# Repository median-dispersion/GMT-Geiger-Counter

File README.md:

# GMT-Geiger-Counter

## ⚠️ DISCLAIMER

This is a hobby project and should not be relied upon to accurately determine radiation levels, especially not if those radiation levels are potentially dangerous and or lethal!

## 🖼️ Images

<p align="center">

    <br>

</p>

## 📸 Screenshots

<p align="center">

</p>

## ⚙️ Features, Settings & Usage

### Geiger counter

#### Main Screen

The main Geiger counter display shows the equivalent dose, a radiation intensity rating, the counts-per-minute reading, and the integration time. From this screen, you can also access and navigate to all other system functions.

| ID     | Description                                                                                                                                                                                                                                                                                                                                                        |
| ------ | ------------------------------------------------------------------------------------------------------------------------------------------------------------------------------------------------------------------------------------------------------------------------------------------------------------------------------------------------------------------ |
| **1**  | **Main Equivalent Dose Screen** - Displays the equivalent dose in your selected unit, calculated over the current integration time.                                                                                                                                                                                                                                |
| **2**  | Tap the equivalent dose display to open the Geiger counter information section.                                                                                                                                                                                                                                                                                    |
| **3**  | Shows the current **radiation rating**.                                                                                                                                                                                                                                                                                                                            |
| **4**  | Displays the **counts per minute (CPM)** reading for the current integration time.                                                                                                                                                                                                                                                                                 |
| **5**  | **Integration Time** - The number of seconds the Geiger counter averages measurements to calculate CPM and equivalent dose. Shorter integration times provide more precise readings at high radiation levels; longer times are better for low radiation levels. The counter automatically adjusts this setting but it can also be manually increased or decreased. |
| **6**  | Tap to open the **audio settings**.                                                                                                                                                                                                                                                                                                                                |
| **7**  | Tap to open the **display settings**.                                                                                                                                                                                                                                                                                                                              |
| **8**  | Tap to enter **sleep mode**, which turns off the display and mutes all buzzer sounds.                                                                                                                                                                                                                                                                              |
| **9**  | Tap to manually **decrease** the integration time.                                                                                                                                                                                                                                                                                                                 |
| **10** | Tap to **reset** the integration time to **automatic**.                                                                                                                                                                                                                                                                                                            |
| **11** | Tap to manually **increase** the integration time.                                                                                                                                                                                                                                                                                                                 |
| **12** | Tap to enable and open the **cosmic ray detector**.                                                                                                                                                                                                                                                                                                                |
| **13** | Tap to view **radiation history** in a graphical format.                                                                                                                                                                                                                                                                                                           |
| **14** | Tap to enable and open the **true random number generator**.                                                                                                                                                                                                                                                                                                       |
| **15** | Tap to open the **hotspot settings**.                                                                                                                                                                                                                                                                                                                              |
| **16** | Tap to open the **Wi-Fi settings**.                                                                                                                                                                                                                                                                                                                                |
| **17** | Tap to open the **system settings**.                                                                                                                                                                                                                                                                                                                               |

#### Geiger counter info screens

The Geiger counter info screen displays additional information about the recorded Geiger counter data, like the absolute number of counts or the total absorbed dose since power-on. In the settings section of this menu, you can also change Geiger counter properties like the measurement unit or if the measured value should auto-range.

| ID    | Descriptions                                                                                                                                                                                              |
| ----- | --------------------------------------------------------------------------------------------------------------------------------------------------------------------------------------------------------- |
| **1** | **Total number of counts / total absorbed dose** - A sum of all counts or the total absorbed dose recorded since the device was powered on. This value only increases when the Geiger counter is enabled. |
| **2** | **Main Tube Detections** - The total number of detections or the total absorbed dose by the main tube since power-on.                                                                                     |
| **3** | **Follower Tube Detections** - The total number of detections or the total absorbed dose by the follower tube since power-on.                                                                             |
| **4** | Tap to **view the previous page.**                                                                                                                                                                        |
| **5** | Tap to **view the next page.**                                                                                                                                                                            |
| **6** | Tap to **exit the Geiger counter info** and return to the Geiger counter screen.                                                                                                                          |

### Cosmic ray detector

The cosmic ray detector measures cosmic ray exposure by recording coincidence events, which are shown on this screen. While the detector is enabled, its data is also available via the serial console, the wireless API interface and the log file.

| ID    | Description                                                                                                                                                                                                                          |
| ----- | ------------------------------------------------------------------------------------------------------------------------------------------------------------------------------------------------------------------------------------ |
| **1** | **Main Coincidence Events Screen** - Shows the total number of coincidence events recorded since the cosmic ray detector was enabled. This value resets when the cosmic ray detector is disabled.                                    |
| **2** | **Coincidence Events per Hour** - Displays the hourly average since the cosmic ray detector was enabled. This value resets when the cosmic ray detector is disabled.                                                                 |
| **3** | **Total Coincidence Events (Since Power-On)** - A sum of all coincidence events recorded since the device was powered on. This value only increases when the cosmic ray detector is enabled, but does not reset when it is disabled. |
| **4** | Tap to **temporarily mute detection sounds**. Tap again to re-enable them. This only mutes regular detection sounds; other alerts will still play.                                                                                   |
| **5** | Tap to enter **sleep mode**, which turns off the display and mutes all buzzer sounds.                                                                                                                                                |
| **6** | **Main Tube Detections** - The total number of detections by the main tube since the cosmic ray detector was enabled. This value resets when the cosmic ray detector is disabled.                                                    |
| **7** | **Follower Tube Detections** - The total number of detections by the follower tube since the cosmic ray detector was enabled. This value resets when the cosmic ray detector is disabled.                                            |
| **8** | Tap to **exit the cosmic ray detector** and return to the Geiger counter screen. A prompt will ask whether to disable the detector or keep it running in the background.                                                             |

### True random number generator

The true random number generator produces truly random numbers. You can set a custom range from 1 to 99, then roll to generate a number, which appears on the main result screen. While the generator is enabled, the Geiger counter is disabled. During this time, a continuous stream of random bits is also available via the serial console and wireless API interface.

| ID     | Description                                                                                                                                        |
| ------ | -------------------------------------------------------------------------------------------------------------------------------------------------- |
| **1**  | **Main Result Screen** - Displays a true random number once the roll is complete.                                                                  |
| **2**  | Tap to **increase the minimum value** of the result range.                                                                                         |
| **3**  | Tap to **increase the maximum value** of the result range.                                                                                         |
| **4**  | Shows the **minimum value** in the result range.                                                                                                   |
| **5**  | Shows the **maximum value** in the result range.                                                                                                   |
| **6**  | Tap to **decrease the minimum value** of the result range.                                                                                         |
| **7**  | Tap to **decrease the maximum value** of the result range.                                                                                         |
| **8**  | Tap to **roll a random number**.                                                                                                                   |
| **9**  | Tap to **temporarily mute detection sounds**. Tap again to re-enable them. This only mutes regular detection sounds; other alerts will still play. |
| **10** | Tap to enter **sleep mode**, which turns off the display and mutes all buzzer sounds.                                                              |
| **11** | Tap to **disable the true random number generator** and return to the Geiger counter screen.                                                       |

## ☁️ Web-App

All data recorded by the Geiger counter can also be accessed through a dedicated web app, which works in any modern browser on both PCs and smartphones. The app’s interface closely mirrors the main display on the Geiger counter itself, while also providing additional features such as extended graphical history with smoothing options. It is also required for tasks like updating Wi-Fi credentials.

To use the web app, an SD card containing the necessary files from the [firmware](Firmware/GMT-Geiger-Counter/SD%20Card/) folder must be inserted. Even without the app, the wireless API remains available, allowing data to be accessed through a browser; however, without the web app, the information will not be presented in a user-friendly format.

Screenshots of the web app can be found in the [screenshots](#-Screenshots) section.

## 🧩 Tube Compatibility

The tube driver PCB is compatible with a variety of Geiger-Müller tubes. Any tube that has a total length including the contacts of **110mm** to **107mm** or **90mm** to **87mm** and operates around **400V DC** should be physically compatible. Here are some tubes that will be compatible with this Geiger counter:

| Tube       | Compatible | Tested | Note                                          |
| ---------- | ---------- | ------ | --------------------------------------------- |
| SBM-20     | ✅          | ✅      | The tube this Geiger counter was designed for |
| STS-5      | ✅          | ❌      | The predecessor tube to the SBM-20            |
| J305 107mm | ✅          | ❌      | A modern alternative to the SBM-20            |
| J305 90mm  | ✅          | ❌      | A shorter version of the J305 107mm           |
| M4011      | ✅          | ❌      | An alternative to the J305 90mm               |

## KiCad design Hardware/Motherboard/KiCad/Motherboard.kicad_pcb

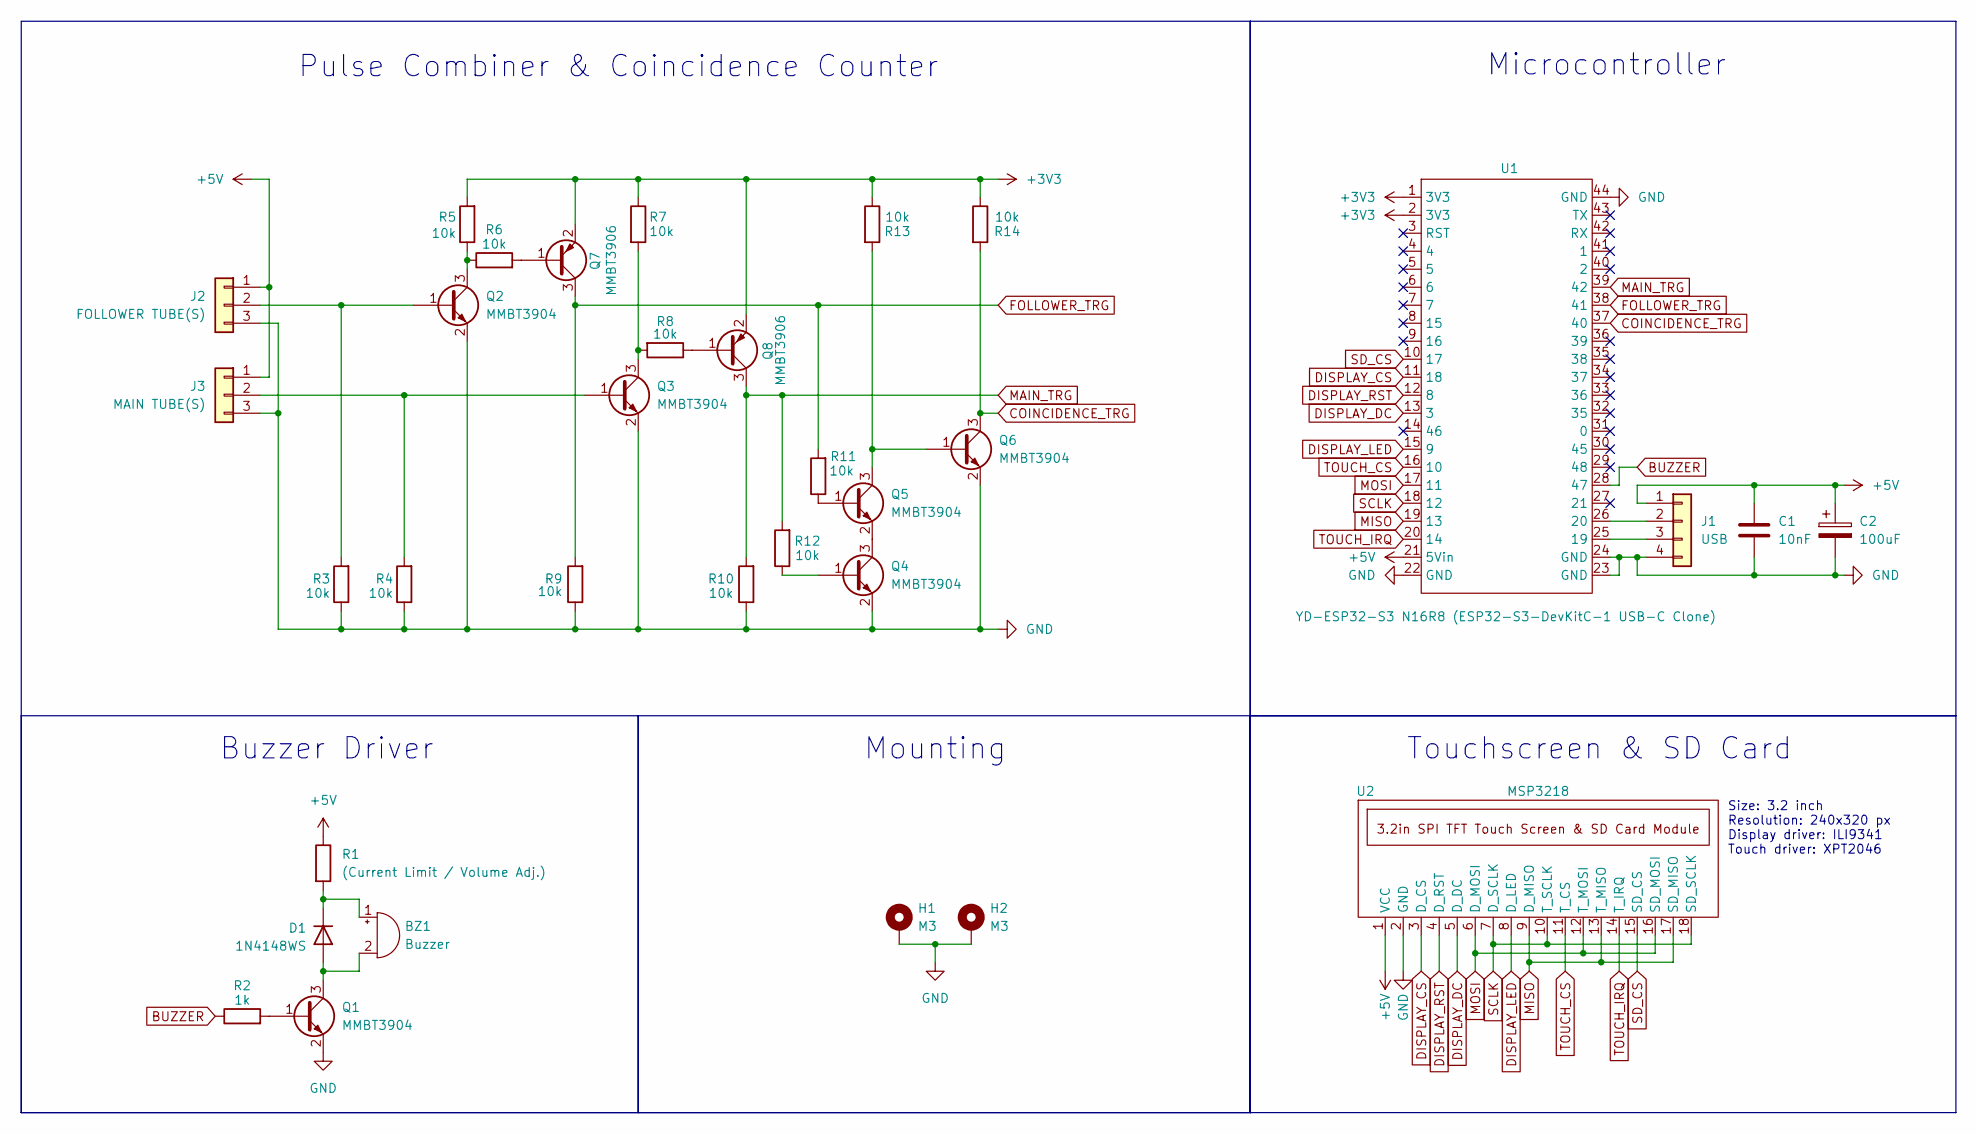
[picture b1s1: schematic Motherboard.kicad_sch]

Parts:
BZ1: Buzzer; PinHeader_1x02_P2.54mm_Vertical; MPN WT-1209T
C1: 10nF; C_1206_3216Metric_Pad1.33x1.80mm_HandSolder; MPN 885012208112
C2: 100uF; CP_Elec_6.3x5.4; MPN 875105344010
D1: 1N4148WS; D_SOD-323_HandSoldering; MPN 1N4148WS
H1, H2: M3; MountingHole_3.2mm_M3_Pad_Via
J1: USB; USB_Pin_Header; MPN PH1RB-04-UA
J2: FOLLOWER TUBE(S); PinHeader_1x03_P2.54mm_Vertical; MPN PH1RB-03-UA
J3: MAIN TUBE(S); PinHeader_1x03_P2.54mm_Vertical; MPN PH1RB-03-UA
Q1, Q2, Q3, Q4, Q5, Q6: MMBT3904; SOT-23_Handsoldering; MPN MMBT3904
Q7, Q8: MMBT3906; SOT-23_Handsoldering; MPN MMBT3906
R1: (Current Limit / Volume Adj.); R_1206_3216Metric_Pad1.30x1.75mm_HandSolder; MPN RC1206JR-070RL
R2: 1k; R_1206_3216Metric_Pad1.30x1.75mm_HandSolder; MPN RC1206FR-071KL
R3, R4, R5, R6, R7, R8, R9, R10, R11, R12, R13, R14: 10k; R_1206_3216Metric_Pad1.30x1.75mm_HandSolder; MPN RC1206FR-1310KL
U1: YD-ESP32-S3 N16R8 (ESP32-S3-DevKitC-1 USB-C Clone); YD-ESP32-S3_(ESP32-S3-DevKitC-1_USB-C_Clone); MPN YD-ESP32-S3 N16R8
U2: MSP3218; 3.2in_SPI_TFT_Touch_Screen_&_SD_Card_Module; MPN MSP3218

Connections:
+3V3: Q7.2 (E), Q8.2 (E), R5.2, R7.1, R13.1, R14.1, U1.1 (3V3), U1.2 (3V3)
+5V: C1.1, C2.1, J1.1, J2.1, J3.1, R1.1, U1.21 (5Vin), U2.1 (VCC)
BUZZER: R2.1, U1.28 (47)
COINCIDENCE_TRG: Q6.3 (C), R14.2, U1.37 (40)
DISPLAY_CS: U1.11 (18), U2.3 (D_CS)
DISPLAY_DC: U1.13 (3), U2.5 (D_DC)
DISPLAY_LED: U1.15 (9), U2.8 (D_LED)
DISPLAY_RST: U1.12 (8), U2.4 (D_RST)
FOLLOWER_TRG: Q7.3 (C), R9.2, R11.2, U1.38 (41)
GND: C1.2, C2.2, H1.1, H2.1, J1.4, J2.3, J3.3, Q1.2 (E), Q2.2 (E), Q3.2 (E), Q4.2 (E), Q6.2 (E), R3.1, R4.1, R9.1, R10.1, U1.22 (GND), U1.23 (GND), U1.24 (GND), U1.44 (GND), U2.2 (GND)
MAIN_TRG: Q8.3 (C), R10.2, R12.2, U1.39 (42)
MISO: U1.19 (13), U2.9 (D_MISO), U2.13 (T_MISO), U2.17 (SD_MISO)
MOSI: U1.17 (11), U2.6 (D_MOSI), U2.12 (T_MOSI), U2.16 (SD_MOSI)
unnamed: BZ1.1 (+), D1.1 (K), R1.2
unnamed: BZ1.2 (-), D1.2 (A), Q1.3 (C)
unnamed: J1.2, U1.26 (20)
unnamed: J1.3, U1.25 (19)
unnamed: J2.2, Q2.1 (B), R3.2
unnamed: J3.2, Q3.1 (B), R4.2
unnamed: Q1.1 (B), R2.2
unnamed: Q2.3 (C), R5.1, R6.1
unnamed: Q3.3 (C), R7.2, R8.2
unnamed: Q4.1 (B), R12.1
unnamed: Q4.3 (C), Q5.2 (E)
unnamed: Q5.1 (B), R11.1
unnamed: Q5.3 (C), Q6.1 (B), R13.2
unnamed: Q7.1 (B), R6.2
unnamed: Q8.1 (B), R8.1
SCLK: U1.18 (12), U2.7 (D_SCLK), U2.10 (T_SCLK), U2.18 (SD_SCLK)
SD_CS: U1.10 (17), U2.15 (SD_CS)
TOUCH_CS: U1.16 (10), U2.11 (T_CS)
TOUCH_IRQ: U1.20 (14), U2.14 (T_IRQ)

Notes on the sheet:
Microcontroller
Mounting
Buzzer Driver
Touchscreen & SD Card
Size: 3.2 inch Resolution: 240x320 px Display driver: ILI9341 Touch driver: XPT2046
Pulse Combiner & Coincidence Counter

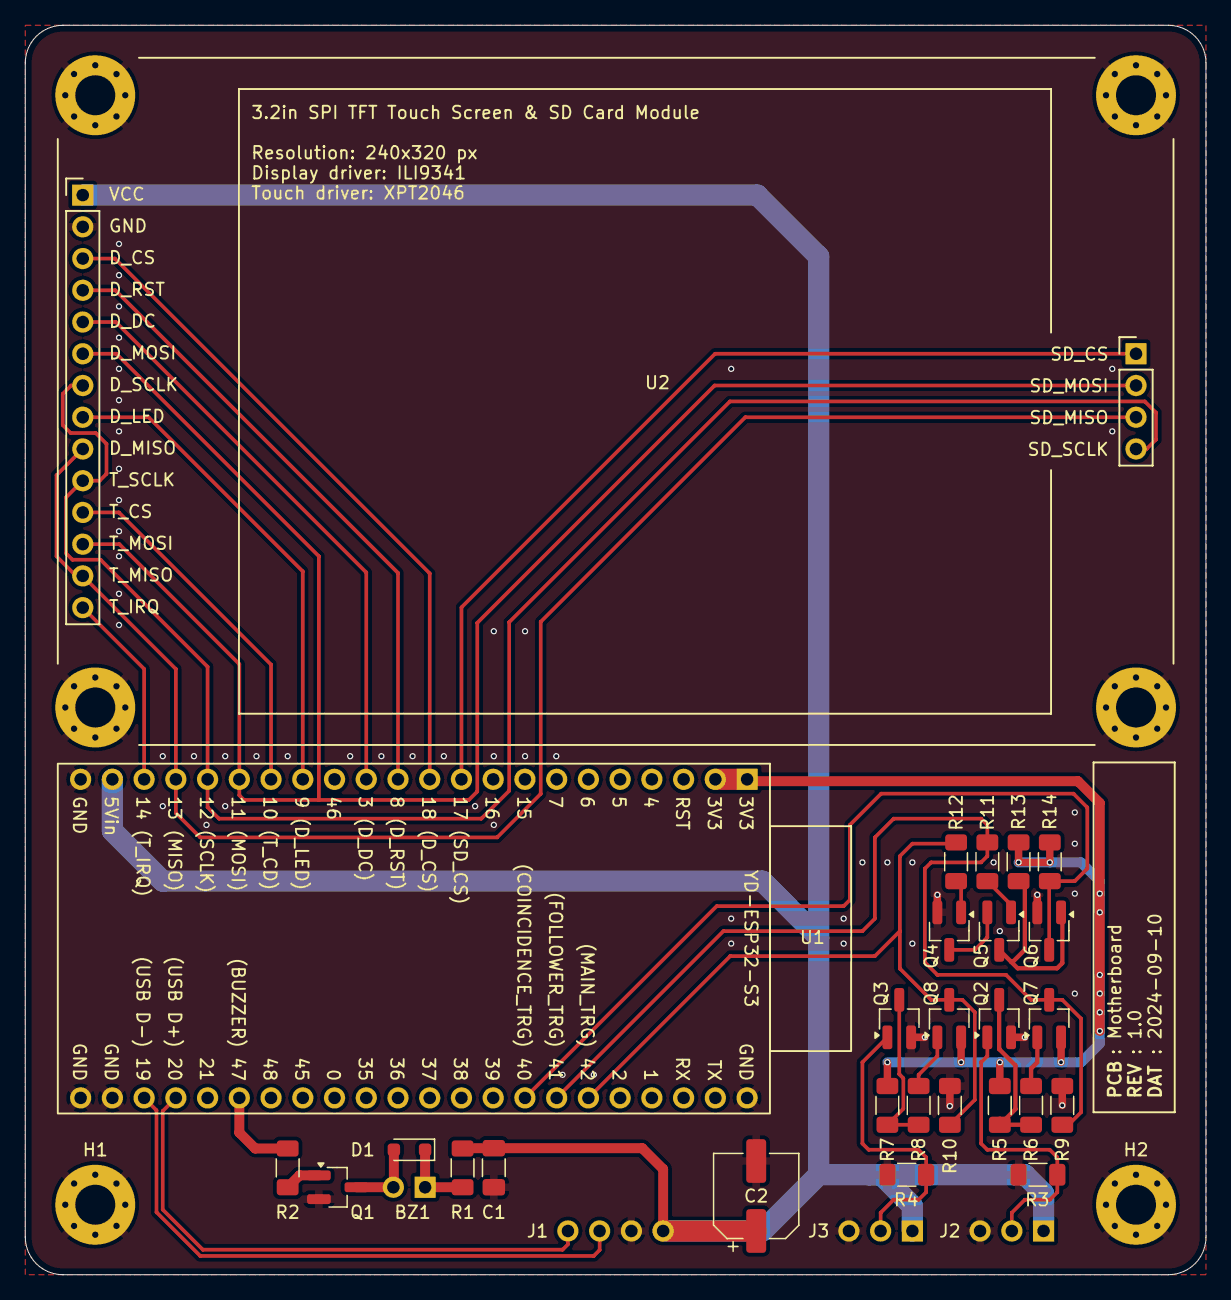
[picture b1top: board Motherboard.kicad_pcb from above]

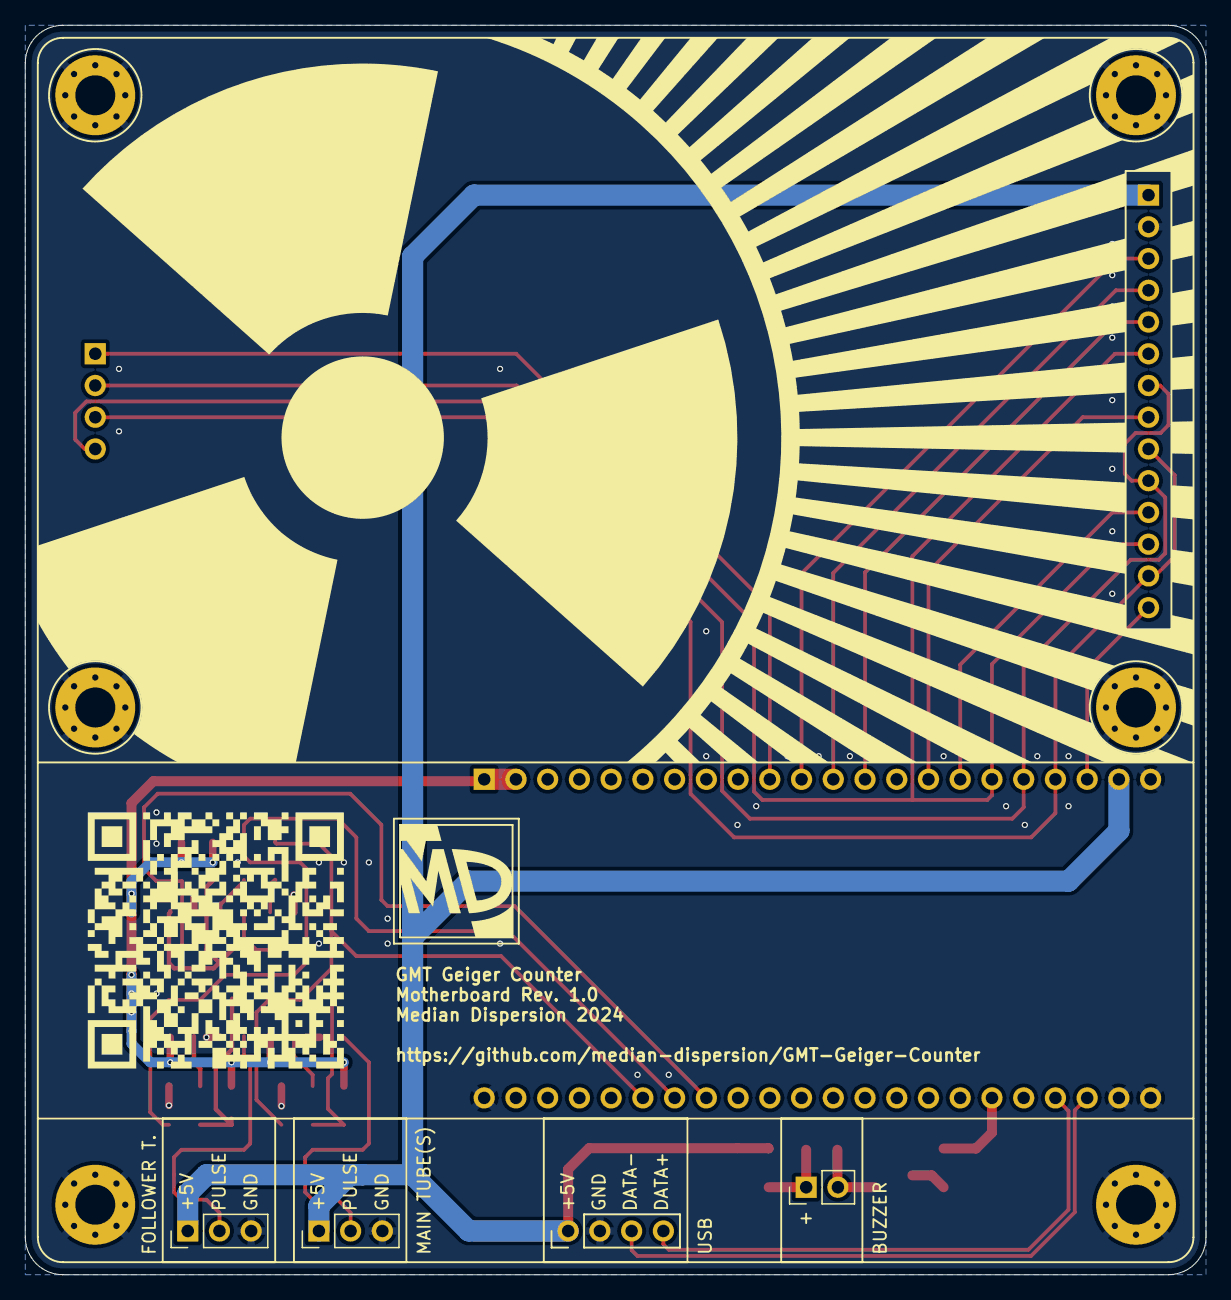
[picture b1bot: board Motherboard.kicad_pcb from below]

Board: 2 copper layers, 94.5 x 100.0 mm, 33 parts (4 on the bottom side), 32 nets.

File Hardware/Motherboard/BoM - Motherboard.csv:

"Reference","Value","Qty","Footprint","MPN","Datasheet","DigiKey","Price (EUR)"
"BZ1","Buzzer","1","Connector_PinHeader_2.54mm:PinHeader_1x02_P2.54mm_Vertical","WT-1209T","https://www.soberton.com/wp-content/uploads/2022/03/WT-1209T.pdf","https://www.digikey.com/en/products/detail/soberton-inc/WT-1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","0,39€"
"C1","10nF","1","Capacitor_SMD:C_1206_3216Metric_Pad1.33x1.80mm_HandSolder","885012208112","https://www.we-online.com/components/products/datasheet/8850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","https://www.digikey.com/en/products/detail/w%C3%BCrth-elektr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 ","0,1€ "
"C2","100uF","1","Capacitor_SMD:CP_Elec_6.3x5.4","875105344010","https://www.we-online.com/components/products/datasheet/8751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","https://www.digikey.com/en/products/detail/würth-elektronik/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 ","0,62€"
"D1","1N4148WS","1","Diode_SMD:D_SOD-323_HandSoldering","1N4148WS","https://www.smc-diodes.com/propdf/1N4148WS%20N0572%20REV.B.pdf","https://www.digikey.com/en/products/detail/smc-diode-solutio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","0,09€"
"J1","USB","1","Footprints:USB_Pin_Header","PH1RB-04-UA","https://app.adam-tech.com/products/download/data_sheet/20128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","https://www.digikey.com/en/products/detail/adam-tech/PH1RB-0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","0,14€"
"J2","FOLLOWER TUBE(S)","1","Connector_PinHeader_2.54mm:PinHeader_1x03_P2.54mm_Vertical","PH1RB-03-UA","https://app.adam-tech.com/products/download/data_sheet/20128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","https://www.digikey.com/en/products/detail/adam-tech/PH1RB-0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","0,11€"
"J3","MAIN TUBE(S)","1","Connector_PinHeader_2.54mm:PinHeader_1x03_P2.54mm_Vertical","PH1RB-03-UA","https://app.adam-tech.com/products/download/data_sheet/20128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","https://www.digikey.com/en/products/detail/adam-tech/PH1RB-0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","0,11€"
"Q1","MMBT3904","1","Package_TO_SOT_SMD:SOT-23_Handsoldering","MMBT3904","https://goodarksemi.com/docs/datasheets/transistors/MMBT3904.pdf","https://www.digikey.com/en/products/detail/good-ark-semicond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","0,09€"
"Q2","MMBT3904","1","Package_TO_SOT_SMD:SOT-23_Handsoldering","MMBT3904","https://goodarksemi.com/docs/datasheets/transistors/MMBT3904.pdf","https://www.digikey.com/en/products/detail/good-ark-semicond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","0,09€"
"Q3","MMBT3904","1","Package_TO_SOT_SMD:SOT-23_Handsoldering","MMBT3904","https://goodarksemi.com/docs/datasheets/transistors/MMBT3904.pdf","https://www.digikey.com/en/products/detail/good-ark-semicond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","0,09€"
"Q4","MMBT3904","1","Package_TO_SOT_SMD:SOT-23_Handsoldering","MMBT3904","https://goodarksemi.com/docs/datasheets/transistors/MMBT3904.pdf","https://www.digikey.com/en/products/detail/good-ark-semicond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","0,09€"
"Q5","MMBT3904","1","Package_TO_SOT_SMD:SOT-23_Handsoldering","MMBT3904","https://goodarksemi.com/docs/datasheets/transistors/MMBT3904.pdf","https://www.digikey.com/en/products/detail/good-ark-semicond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","0,09€"
"Q6","MMBT3904","1","Package_TO_SOT_SMD:SOT-23_Handsoldering","MMBT3904","https://goodarksemi.com/docs/datasheets/transistors/MMBT3904.pdf","https://www.digikey.com/en/products/detail/good-ark-semicond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","0,09€"
"Q7","MMBT3906","1","Package_TO_SOT_SMD:SOT-23_Handsoldering","MMBT3906","https://goodarksemi.com/docs/datasheets/transistors/MMBT3906.pdf","https://www.digikey.com/en/products/detail/good-ark-semicond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","0,09€"
"Q8","MMBT3906","1","Package_TO_SOT_SMD:SOT-23_Handsoldering","MMBT3906","https://goodarksemi.com/docs/datasheets/transistors/MMBT3906.pdf","https://www.digikey.com/en/products/detail/good-ark-semicond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","0,09€"
"R1","(Current Limit / Volume Adj.)","1","Resistor_SMD:R_1206_3216Metric_Pad1.30x1.75mm_HandSolder","RC1206JR-070RL","https://www.yageo.com/upload/media/product/products/datashee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","https://www.digikey.com/en/products/detail/yageo/RC1206JR-07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","0,09€"
"R2","1k","1","Resistor_SMD:R_1206_3216Metric_Pad1.30x1.75mm_HandSolder","RC1206FR-071KL","https://www.yageo.com/upload/media/product/products/datashee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","https://www.digikey.com/en/products/detail/yageo/RC1206FR-07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","0,09€"
"R3","10k","1","Resistor_SMD:R_1206_3216Metric_Pad1.30x1.75mm_HandSolder","RC1206FR-1310KL","https://www.yageo.com/upload/media/product/products/datashee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","https://www.digikey.com/en/products/detail/yageo/RC1206FR-13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","0,09€"
"R4","10k","1","Resistor_SMD:R_1206_3216Metric_Pad1.30x1.75mm_HandSolder","RC1206FR-1310KL","https://www.yageo.com/upload/media/product/products/datashee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","https://www.digikey.com/en/products/detail/yageo/RC1206FR-13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","0,09€"
"R5","10k","1","Resistor_SMD:R_1206_3216Metric_Pad1.30x1.75mm_HandSolder","RC1206FR-1310KL","https://www.yageo.com/upload/media/product/products/datashee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","https://www.digikey.com/en/products/detail/yageo/RC1206FR-13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","0,09€"
"R6","10k","1","Resistor_SMD:R_1206_3216Metric_Pad1.30x1.75mm_HandSolder","RC1206FR-1310KL","https://www.yageo.com/upload/media/product/products/datashee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","https://www.digikey.com/en/products/detail/yageo/RC1206FR-13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","0,09€"
"R7","10k","1","Resistor_SMD:R_1206_3216Metric_Pad1.30x1.75mm_HandSolder","RC1206FR-1310KL","https://www.yageo.com/upload/media/product/products/datashee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","https://www.digikey.com/en/products/detail/yageo/RC1206FR-13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","0,09€"
"R8","10k","1","Resistor_SMD:R_1206_3216Metric_Pad1.30x1.75mm_HandSolder","RC1206FR-1310KL","https://www.yageo.com/upload/media/product/products/datashee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","https://www.digikey.com/en/products/detail/yageo/RC1206FR-13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","0,09€"
"R9","10k","1","Resistor_SMD:R_1206_3216Metric_Pad1.30x1.75mm_HandSolder","RC1206FR-1310KL","https://www.yageo.com/upload/media/product/products/datashee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","https://www.digikey.com/en/products/detail/yageo/RC1206FR-13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","0,09€"
"R10","10k","1","Resistor_SMD:R_1206_3216Metric_Pad1.30x1.75mm_HandSolder","RC1206FR-1310KL","https://www.yageo.com/upload/media/product/products/datashee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","https://www.digikey.com/en/products/detail/yageo/RC1206FR-13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","0,09€"
"R11","10k","1","Resistor_SMD:R_1206_3216Metric_Pad1.30x1.75mm_HandSolder","RC1206FR-1310KL","https://www.yageo.com/upload/media/product/products/datashee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","https://www.digikey.com/en/products/detail/yageo/RC1206FR-13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","0,09€"
"R12","10k","1","Resistor_SMD:R_1206_3216Metric_Pad1.30x1.75mm_HandSolder","RC1206FR-1310KL","https://www.yageo.com/upload/media/product/products/datashee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","https://www.digikey.com/en/products/detail/yageo/RC1206FR-13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","0,09€"
"R13","10k","1","Resistor_SMD:R_1206_3216Metric_Pad1.30x1.75mm_HandSolder","RC1206FR-1310KL","https://www.yageo.com/upload/media/product/products/datashee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","https://www.digikey.com/en/products/detail/yageo/RC1206FR-13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","0,09€"
"R14","10k","1","Resistor_SMD:R_1206_3216Metric_Pad1.30x1.75mm_HandSolder","RC1206FR-1310KL","https://www.yageo.com/upload/media/product/products/datashee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","https://www.digikey.com/en/products/detail/yageo/RC1206FR-13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","0,09€"
"U1","YD-ESP32-S3 N16R8 (ESP32-S3-DevKitC-1 USB-C Clone)","1","Footprints:YD-ESP32-S3_(ESP32-S3-DevKitC-1_USB-C_Clone)","YD-ESP32-S3 N16R8","https://github.com/vcc-gnd/YD-ESP32-S3","~","8€"
"U2","MSP3218","1","Footprints:3.2in_SPI_TFT_Touch_Screen_&_SD_Card_Module","MSP3218","~","~","12€"

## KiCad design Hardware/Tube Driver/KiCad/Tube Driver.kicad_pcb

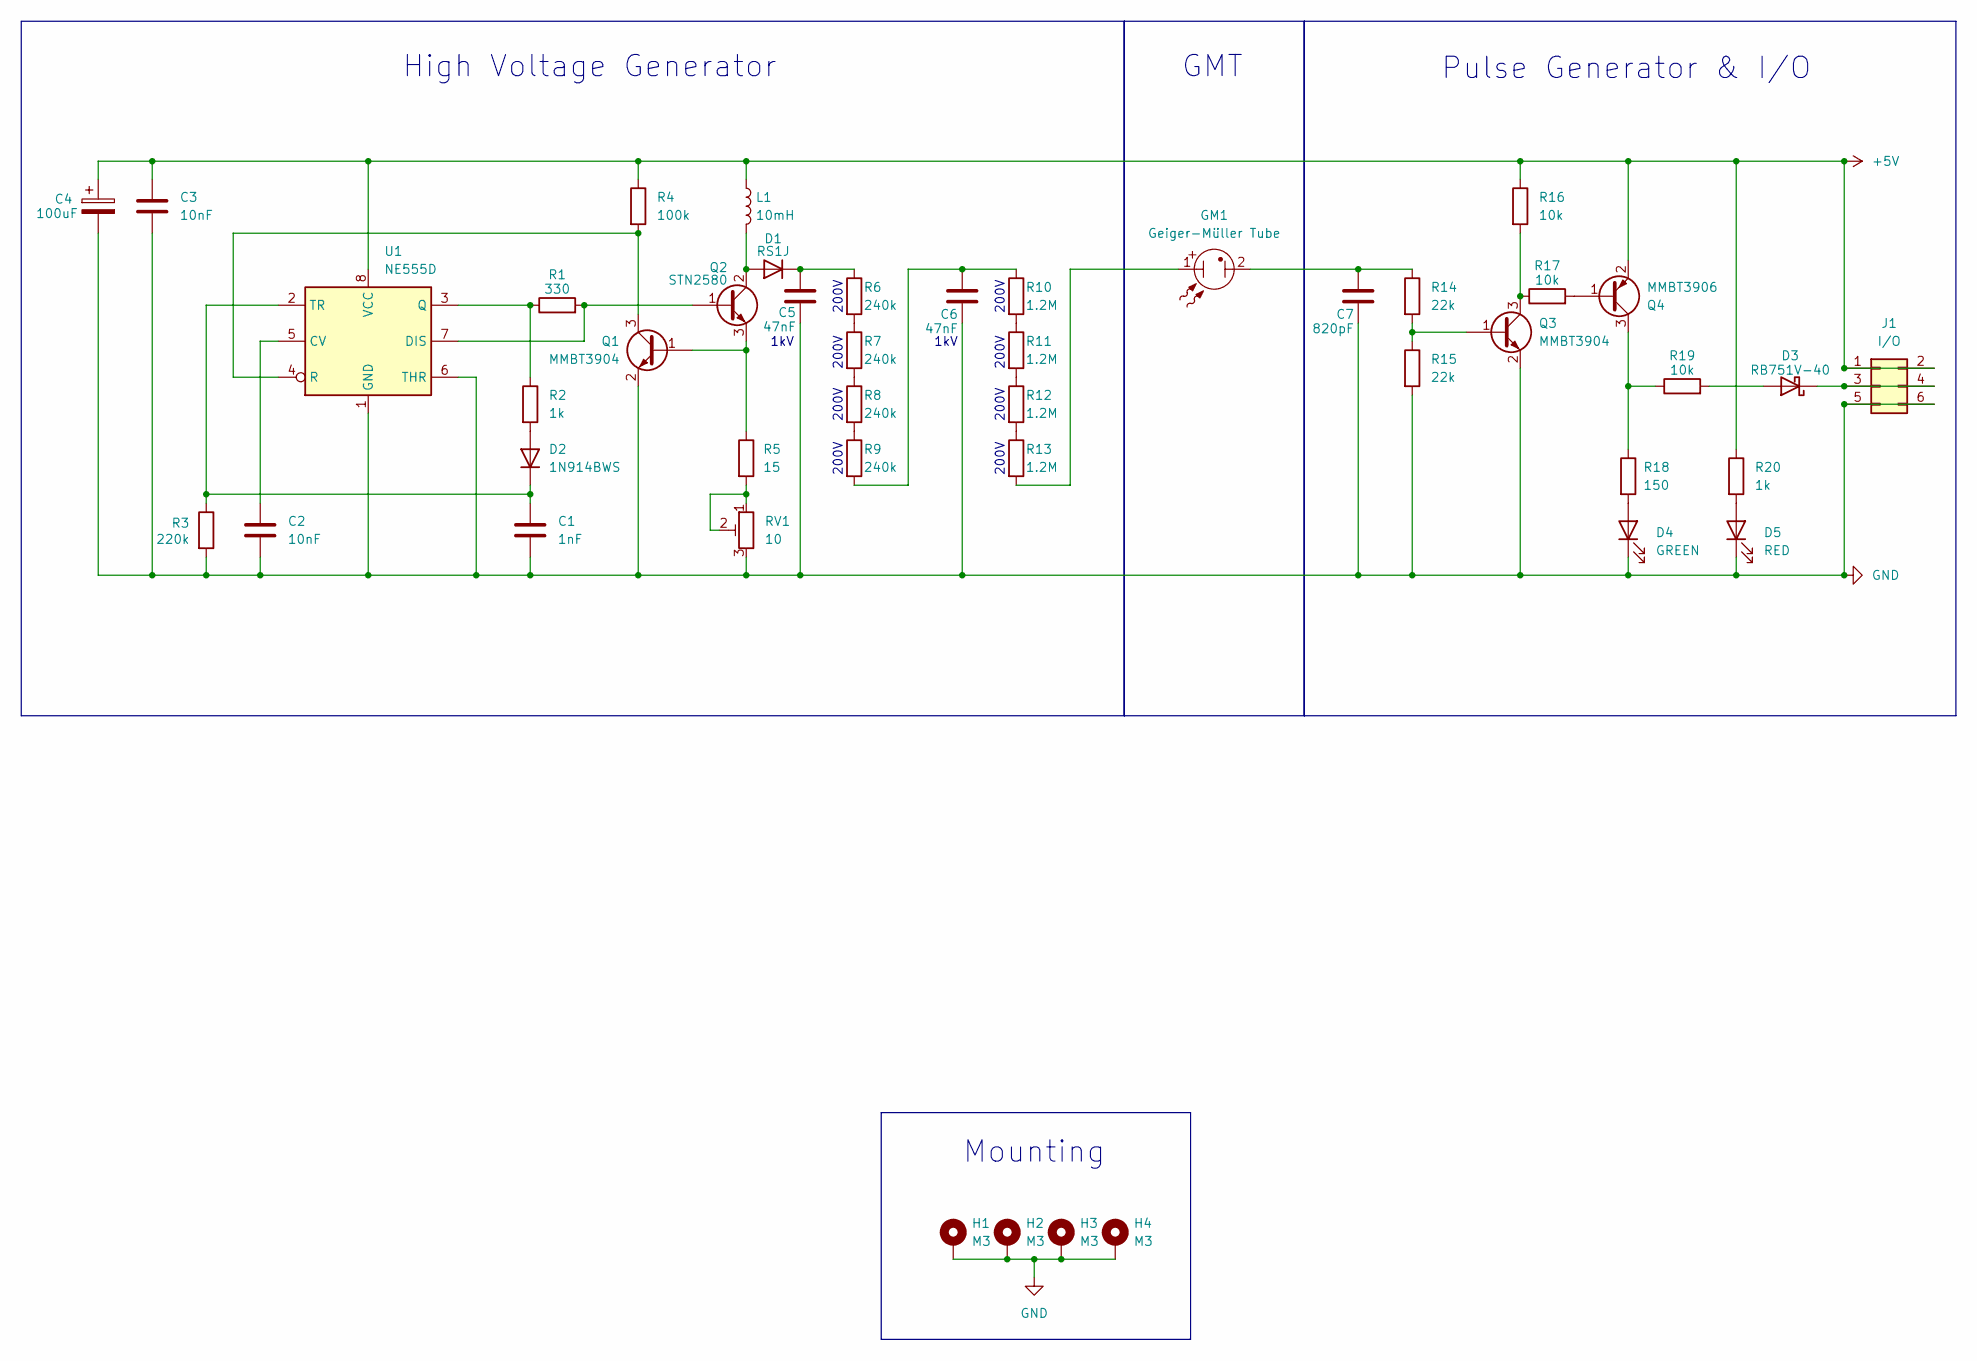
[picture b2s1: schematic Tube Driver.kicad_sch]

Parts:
C1: 1nF; C_1206_3216Metric_Pad1.33x1.80mm_HandSolder; MPN 885012208046
C2, C3: 10nF; C_1206_3216Metric_Pad1.33x1.80mm_HandSolder; MPN 885012208112
C4: 100uF; CP_Elec_6.3x5.4; MPN 865080243007
C5, C6: 47nF; C_1210_3225Metric_Pad1.33x2.70mm_HandSolder; MPN C1210V473KDRAC7800
C7: 820pF; C_1206_3216Metric_Pad1.33x1.80mm_HandSolder; MPN CC1206FRNPO9BN821
D1: RS1J; D_SMA_HV_Handsoldering; MPN RS1J-13-F
D2: 1N914BWS; D_SOD-323_HandSoldering; MPN 1N914BWS
D3: RB751V-40; D_SOD-323_HandSoldering; MPN RB751V-40_R1_00001
D4: GREEN; LED_1206_3216Metric_Pad1.42x1.75mm_HandSolder; MPN 150120GS75000
D5: RED; LED_1206_3216Metric_Pad1.42x1.75mm_HandSolder; MPN 150120RS75000
GM1: Geiger-Müller Tube; GM_Tube_Mount; MPN FC-102 BRIGHT TIN
H1, H2, H3, H4: M3; MountingHole_3.2mm_M3_Pad_Via
J1: I/O; PinHeader_2x03_P2.54mm_Vertical; MPN PH2-06-UA
L1: 10mH; L_8065_HandSolder; MPN 74404086103
Q1, Q3: MMBT3904; SOT-23_Handsoldering; MPN MMBT3904
Q2: STN2580; SOT-223; MPN STN2580
Q4: MMBT3906; SOT-23_Handsoldering; MPN MMBT3906
R1: 330; R_1206_3216Metric_Pad1.30x1.75mm_HandSolder; MPN RC1206FR-07330RL
R2, R20: 1k; R_1206_3216Metric_Pad1.30x1.75mm_HandSolder; MPN RC1206FR-071KL
R3: 220k; R_1206_3216Metric_Pad1.30x1.75mm_HandSolder; MPN RC1206FR-07220KL
R4: 100k; R_1206_3216Metric_Pad1.30x1.75mm_HandSolder; MPN AC1206FR-07100KL
R5: 15; R_1206_3216Metric_Pad1.30x1.75mm_HandSolder; MPN RC1206FR-0715RL
R6, R7, R8, R9: 240k; R_1206_3216Metric_Pad1.30x1.75mm_HandSolder; MPN RC1206FR-07240KL
R10, R11, R12, R13: 1.2M; R_1206_3216Metric_Pad1.30x1.75mm_HandSolder; MPN RC1206FR-071M2L
R14, R15: 22k; R_1206_3216Metric_Pad1.30x1.75mm_HandSolder; MPN RC1206FR-0722KL
R16, R17, R19: 10k; R_1206_3216Metric_Pad1.30x1.75mm_HandSolder; MPN RC1206FR-1310KL
R18: 150; R_1206_3216Metric_Pad1.30x1.75mm_HandSolder; MPN RC1206FR-13150RL
RV1: 10; RV_3361P; MPN 3361P-1-100GLF
U1: NE555D; SOIC-8_3.9x4.9mm_P1.27mm; MPN NE555D

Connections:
+5V: C3.1, C4.1, J1.1, J1.2, L1.1, Q4.2 (E), R4.1, R16.1, R20.1, U1.8 (VCC)
GND: C1.2, C2.2, C3.2, C4.2, C5.2, C6.2, C7.2, D4.1 (K), D5.1 (K), H1.1, H2.1, H3.1, H4.1, J1.5, J1.6, Q1.2 (E), Q3.2 (E), R3.2, R15.2, RV1.3, U1.1 (GND), U1.6 (THR)
unnamed: C6.1, R9.2, R10.1
unnamed: C7.1, GM1.2, R14.1
unnamed: D1.2 (A), L1.2, Q2.2 (C), Q2.4 (C)
unnamed: C5.1, D1.1 (K), R6.1
unnamed: D2.2 (A), R2.2
unnamed: C1.1, D2.1 (K), R3.1, U1.2 (TR)
unnamed: D3.2 (A), R19.2
unnamed: D3.1 (K), J1.3, J1.4
unnamed: D4.2 (A), R18.2
unnamed: D5.2 (A), R20.2
unnamed: GM1.1, R13.2
unnamed: Q1.1 (B), Q2.3 (E), R5.1
unnamed: Q1.3 (C), R4.2, U1.4 (R)
unnamed: Q2.1 (B), R1.2, U1.7 (DIS)
unnamed: Q3.1 (B), R14.2, R15.1
unnamed: Q3.3 (C), R16.2, R17.1
unnamed: Q4.1 (B), R17.2
unnamed: Q4.3 (C), R18.1, R19.1
unnamed: R5.2, RV1.1, RV1.2
unnamed: R6.2, R7.1
unnamed: R7.2, R8.1
unnamed: R8.2, R9.1
unnamed: R10.2, R11.1
unnamed: R11.2, R12.1
unnamed: R12.2, R13.1
unnamed: C2.1, U1.5 (CV)
unnamed: R1.1, R2.1, U1.3 (Q)

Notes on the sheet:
200V
1kV
GMT
High Voltage Generator
Mounting
Pulse Generator & I/O
